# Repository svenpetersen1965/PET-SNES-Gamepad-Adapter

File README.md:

# PET-SNES-Gamepad-Adapter
An Adapter for connecting the SNES Gamepad to the userport of the Commodore PET/CBM/C64/VIC20

This adapter is capable of playing PETSCII robots and other SNES Gamepad compatible games on the Commodore PET. It was further tested playing the forementioned game on the C64.

There is a Rev. 1, which can be switched to use the +5V of the C64 User Port, so no diagnostic cassette dongle or external PSU is required for powering the gamepad. 

<b>!!!WARNING: Setting the power selection switch to C64 and connect the device to a PET might damage the computer!!!</b> 

It is recommended to leave the switch not populated in case you are planning to coonect the device to a PET. If you have a PET, check the setting each time, before you connect ther device to the PET. 

Recommended screws:<br>
Four each of 2.9mm x 9.5mm (self taping) screws for sheet metal (C 2,9x9,5H, DIN 7981).

The BOM value of Rev. 1 is 14,95€ (2026-07-21) without the cassette dongle, a case and or shipping fees or tariffs .

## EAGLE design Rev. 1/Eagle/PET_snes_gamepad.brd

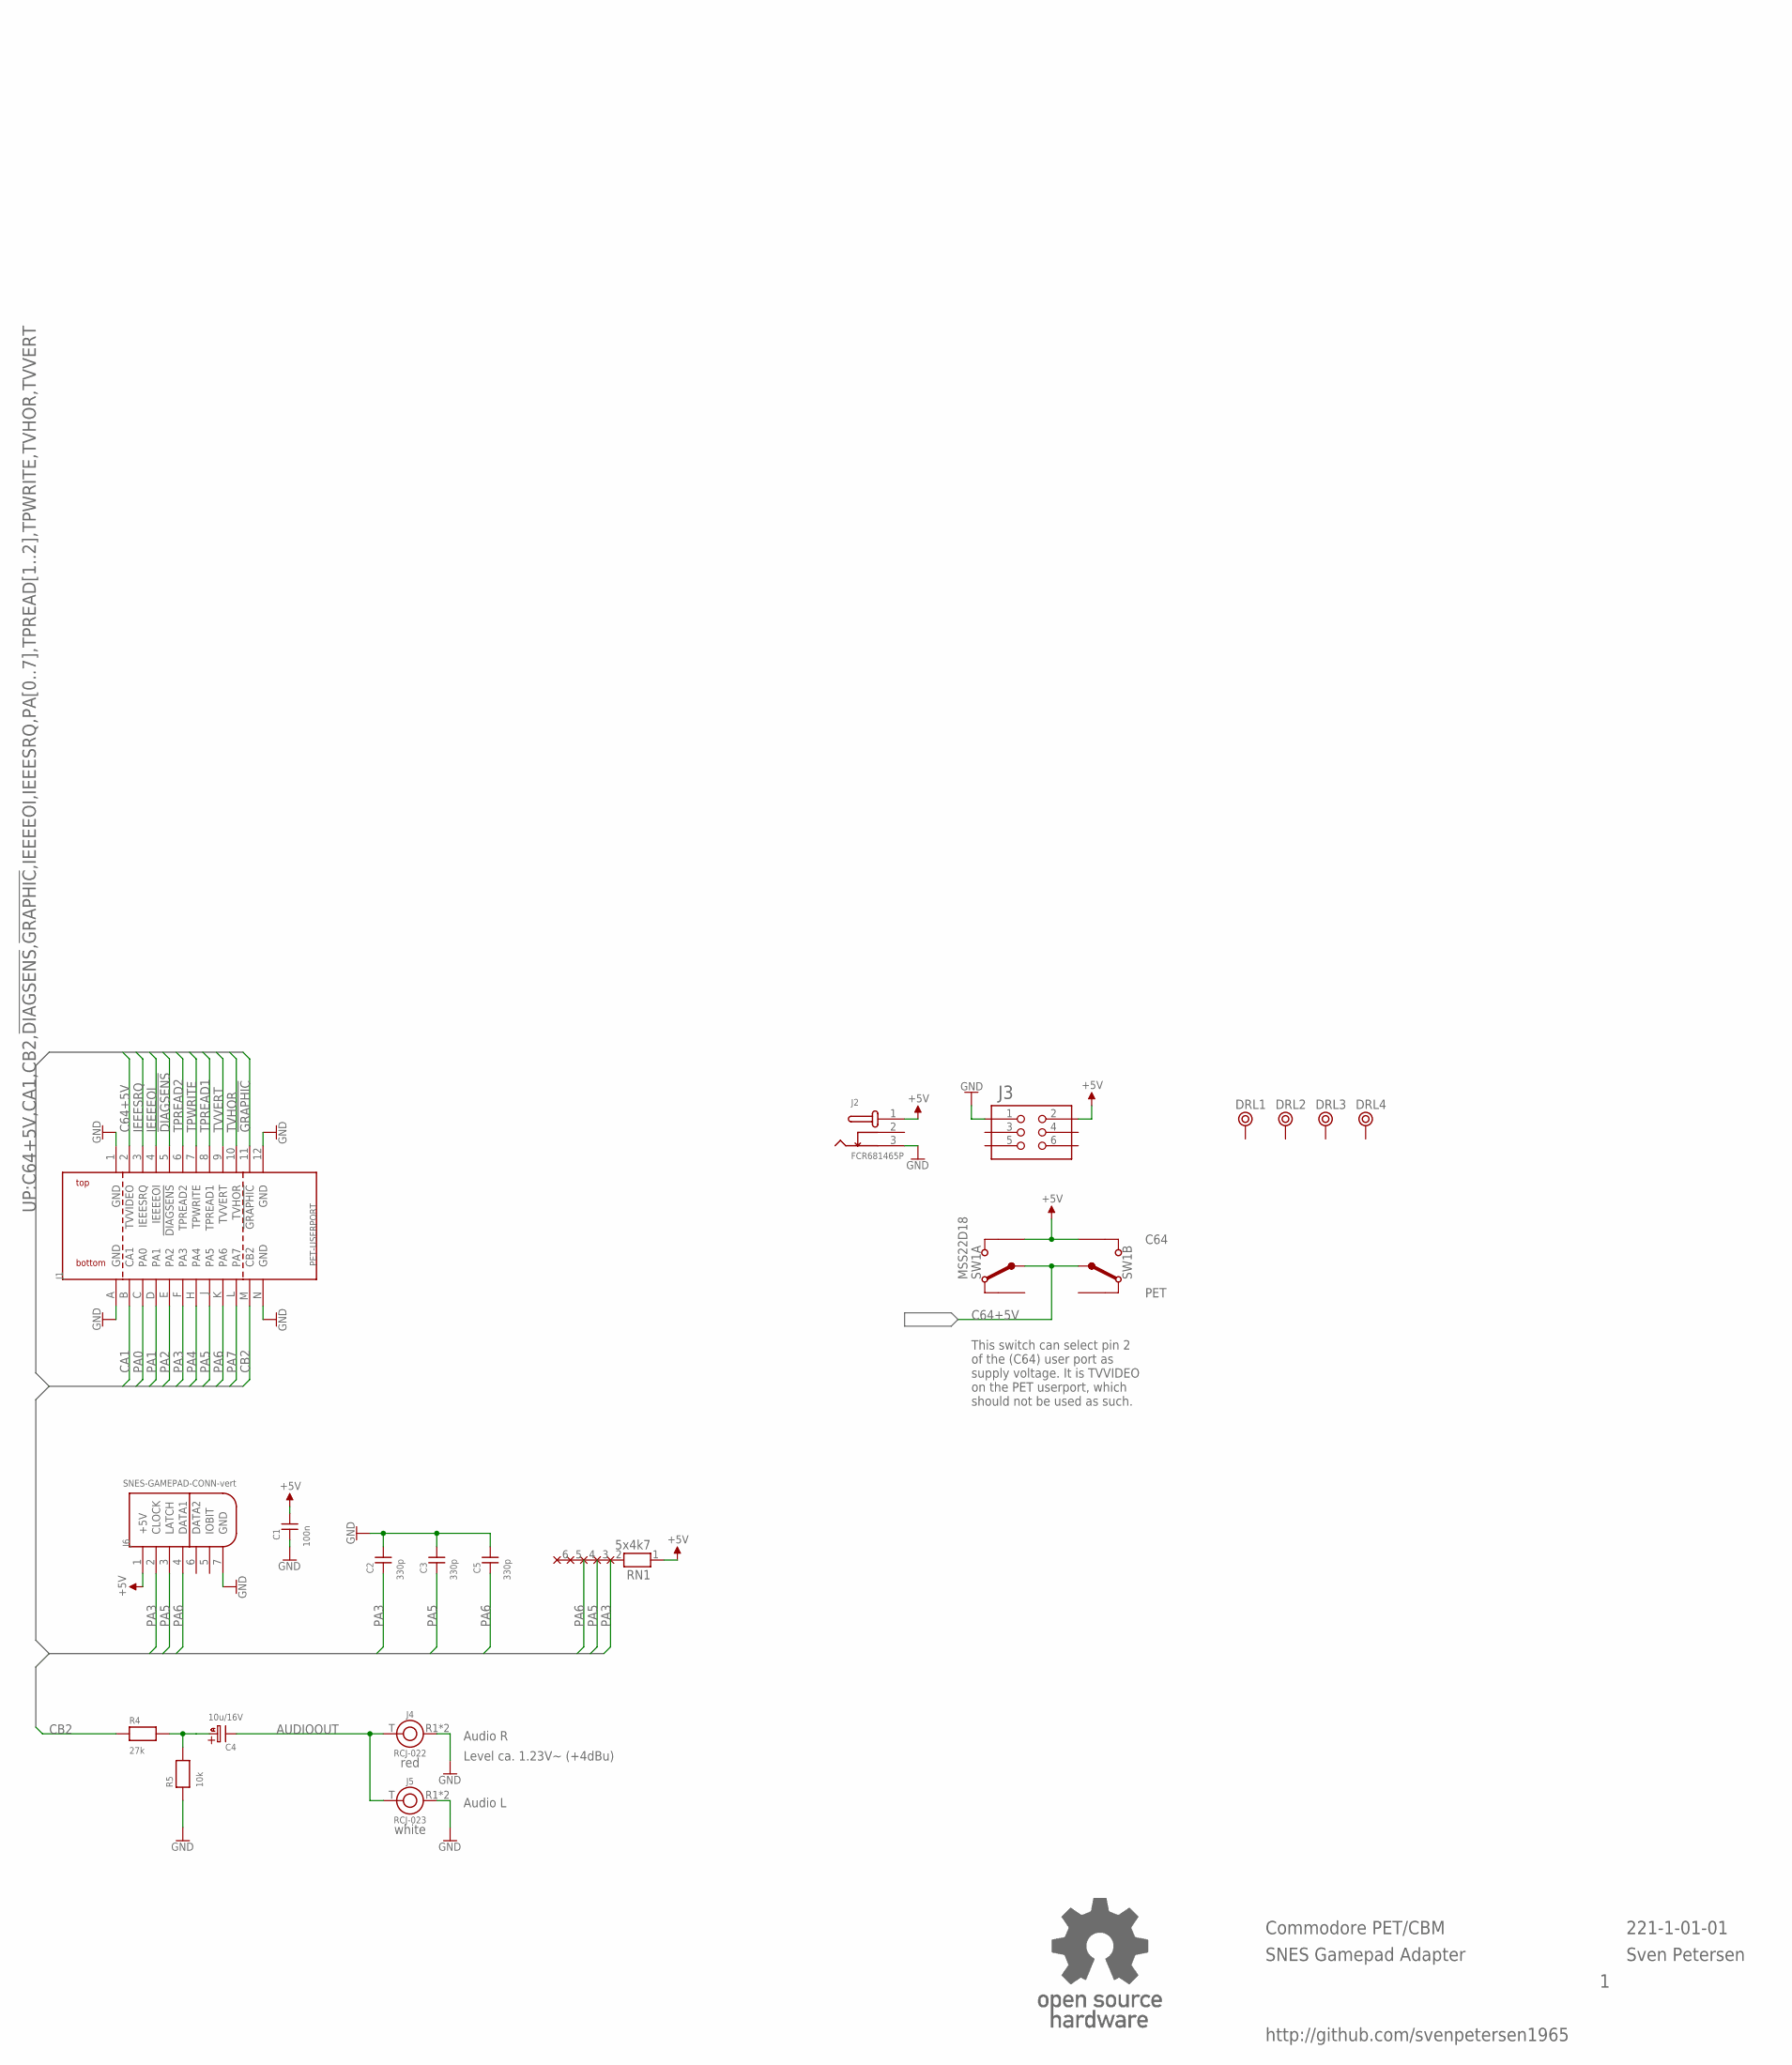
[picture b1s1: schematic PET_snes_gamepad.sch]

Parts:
C1: 100n; C-2,5
C2, C3, C5: 330p; C-2,5
C4: 10u/16V; C5,0/2,0
DRL1, DRL2, DRL3, DRL4: BOHR3,5
J1: PET-USERPORT; USERPORT
J2: FCR681465P
J3: 2X03WV
J4: RCJ-022; RCJ-02X
J5: RCJ-023; RCJ-02X
J6: SNES-GAMEPAD-CONN-vert; SNES_GAMEPAD_VERT
R4: 27k; R-10
R5: 10k; R-10
RN1: 5x4k7; RN-6
SW1: MSS22D18; DPDT_9MM
U$2: OPEN_SOURCE_HW; OPENHW

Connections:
!DIAGSENS: J1.5 (!DIAGSENS)
!GRAPHIC: J1.11 (!GRAPHIC)
+5V: C1.2, J2.1, J3.2, J6.1 (+5V), RN1.1, SW1.1 (UP), SW1.6 (UP)
AUDIOOUT: C4.K (-), J4.T, J5.T
C64+5V: J1.2 (TVVIDEO), SW1.2 (COM), SW1.5 (COM)
CA1: J1.B (CA1)
CB2: J1.M (CB2), R4.1
GND: C1.1, C2.2, C3.2, C5.2, J1.1 (GND), J1.12 (GND), J1.A (GND), J1.N (GND), J2.3, J3.1, J4.R1 (R), J4.R2 (R), J5.R1 (R), J5.R2 (R), J6.7 (GND), R5.1
IEEEEOI: J1.4 (IEEEEOI)
IEEESRQ: J1.3 (IEEESRQ)
unnamed: C4.A (+), R4.2, R5.2
PA0: J1.C (PA0)
PA1: J1.D (PA1)
PA2: J1.E (PA2)
PA3: C2.1, J1.F (PA3), J6.2 (CLOCK), RN1.2
PA4: J1.H (PA4)
PA5: C3.1, J1.J (PA5), J6.3 (LATCH), RN1.3
PA6: C5.1, J1.K (PA6), J6.4 (DATA1), RN1.4
PA7: J1.L (PA7)
TPREAD1: J1.8 (TPREAD1)
TPREAD2: J1.6 (TPREAD2)
TPWRITE: J1.7 (TPWRITE)
TVHOR: J1.10 (TVHOR)
TVVERT: J1.9 (TVVERT)

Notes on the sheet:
http://github.com/svenpetersen1965
Commodore PET/CBM
SNES Gamepad Adapter
Sven Petersen
221-1-01-01
red
white
Audio R
Audio L
Level ca. 1.23V~ (+4dBu)
PET
C64
This switch can select pin 2 of the (C64) user port as supply voltage. It is TVVIDEO on the PET userport, which should not be used as such.

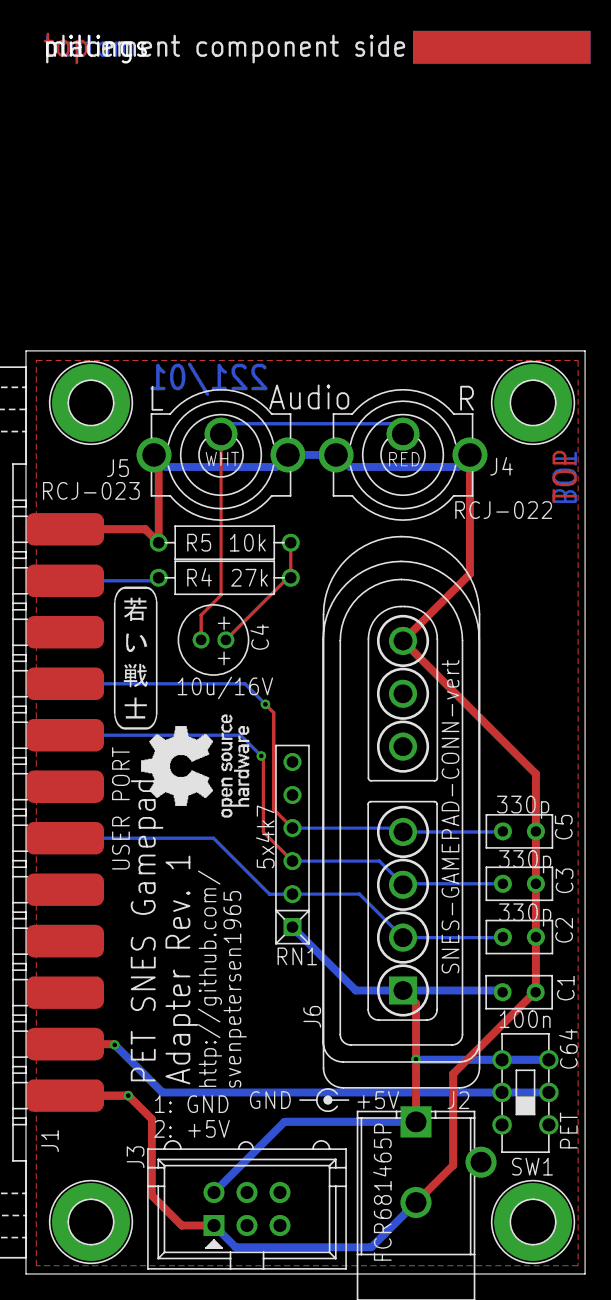
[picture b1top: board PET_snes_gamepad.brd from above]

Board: 2 copper layers, 43.0 x 71.0 mm, 23 parts (0 on the bottom side), 9 nets.

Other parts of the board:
U$11: 2LAYER
U$22: PCB-TITLE/
U$26: SVEN_TAG

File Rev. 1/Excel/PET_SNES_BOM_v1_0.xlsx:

PET SNES Gamepad Adapter Rev. 1
Bill of Material Rev. 1.0
Pos. | Qty | Value | Footprint | Ref.-No. | Comment
1 | 1 | 221-2-01-00 | 2 Layer | _PCB Rev. 0 | 2 layer, Cu 35µ, HASL, 71.0mm x 43.0mm, 1.6mm FR4
2 | 1 | 100n | C-2,5 | C1 | ceramic capacitor, pitch: 2.5mm
3 | 3 | 330p | C-2,5 | C2, C3, C5 | ceramic capacitor, pitch: 2.5mm
4 | 1 | 10u/16V | C5,0/2,0 | C4 | aluminum electrolytic, Æ5.0mm/pitch 2.0mm 105°C, l=11mm, e.G. Reichelt RD1C106M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
5 | 1 | Edge connector, 2x12, 3.96mm | USERPORT | J1 | edge connector, C64 user port, Ali Express, "series 805" or other
6 | 1 | FCR681465P | FCR681465P | J2 | Cliff. 2,5mm/5.5mm barrel connector. E.g. Reichelt CLIFF FCR681465P
7 | 1 | 2x3 box header, 2.54mm | 2X03WV | J3 | e.g. Reichelt WSL 6G.
8 | 1 | RCJ-022 | RCJ-02X | J4 | CUI Inc., RCA jack, vertical, red. Mouser: 490-RCJ-022, Digikey: CP-1407-ND. Al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
9 | 1 | RCJ-023 | RCJ-02X | J5 | CUI Inc., RCA jack, vertical, white. Mouser: 490-RCJ-023, Digikey: CP-1408-ND. 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
10 | 1 | SNES-GAMEPAD-CONN-vert | SNES_GAMEPAD_VERT | J6 | Vertical SNES Gamepad Connector from Ali Express
11 | 1 | 27k | R-10 | R4 | 1/4W, 1% or better
12 | 1 | 10k | R-10 | R5 | 1/4W, 1% or better
13 | 1 | 5x4k7 | RN-6 | RN1 | Resistor network 4 pin, 5 resistors
14 | 1 | mini slide switch, 2.54mm, DPDT, through hole | DPDT_9MM | SW1 | Ali Express, ebay, Amazon, search term "MSS22D18"
